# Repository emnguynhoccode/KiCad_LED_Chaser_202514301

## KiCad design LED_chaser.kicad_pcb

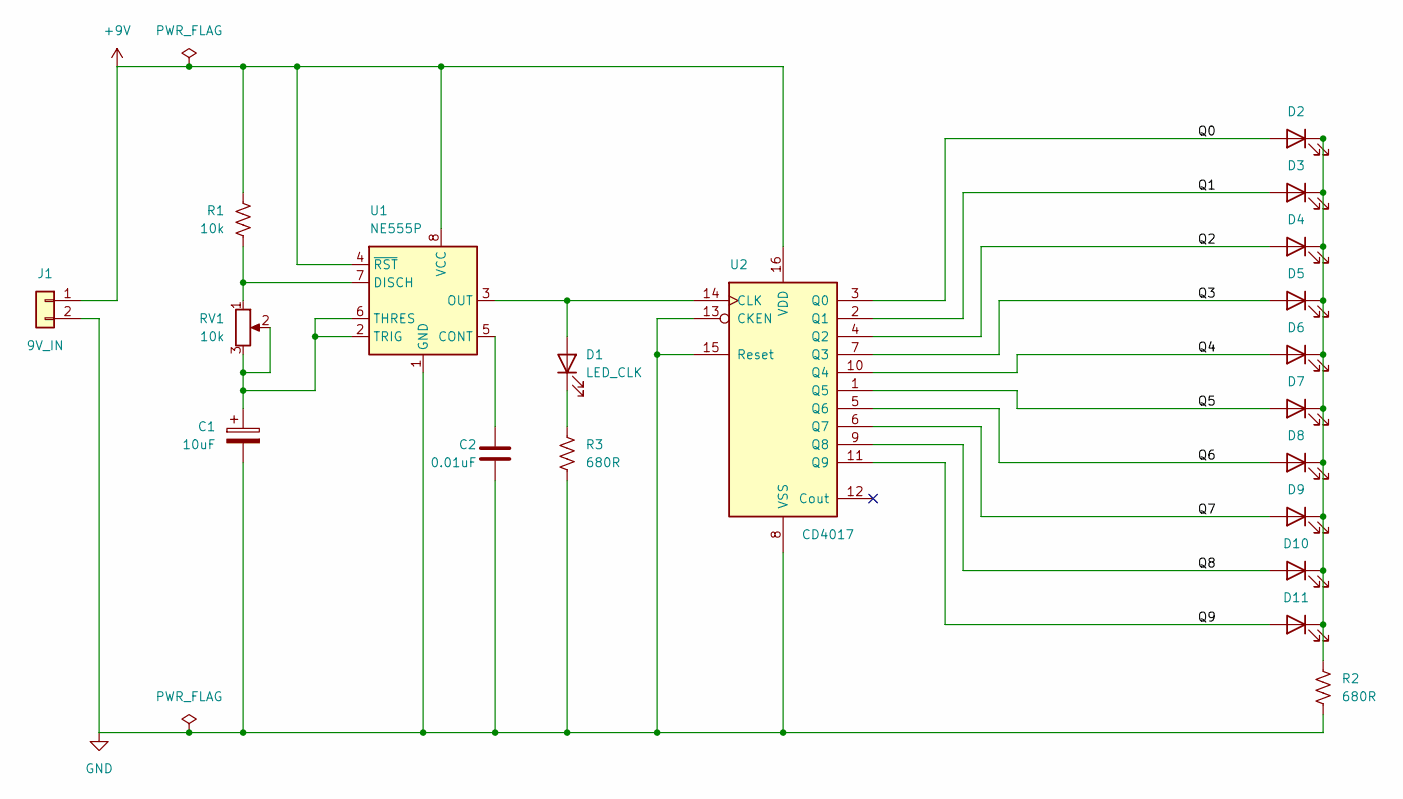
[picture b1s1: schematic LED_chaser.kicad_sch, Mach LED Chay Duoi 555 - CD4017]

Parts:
C1: 10uF; CP_Radial_D5.0mm_P2.50mm
C2: 0.01uF; C_Disc_D5.0mm_W2.5mm_P2.50mm
D1: LED_CLK; LED_D5.0mm
D2, D3, D4, D5, D6, D7, D8, D9, D10, D11: LED; LED_D5.0mm
J1: 9V_IN; PinHeader_1x02_P2.54mm_Vertical
R1: 10k; R_Axial_DIN0207_L6.3mm_D2.5mm_P10.16mm_Horizontal
R2, R3: 680R; R_Axial_DIN0207_L6.3mm_D2.5mm_P10.16mm_Horizontal
RV1: 10k; Potentiometer_Bourns_3386P_Vertical
U1: NE555P; DIP-8_W7.62mm
U2: CD4017; DIP-16_W7.62mm

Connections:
+9V: J1.1, R1.1, U1.4 (~RST), U1.8 (VCC), U2.16 (VDD)
/Q0: D2.2 (A), U2.3 (Q0)
/Q1: D3.2 (A), U2.2 (Q1)
/Q2: D4.2 (A), U2.4 (Q2)
/Q3: D5.2 (A), U2.7 (Q3)
/Q4: D6.2 (A), U2.10 (Q4)
/Q5: D7.2 (A), U2.1 (Q5)
/Q6: D8.2 (A), U2.5 (Q6)
/Q7: D9.2 (A), U2.6 (Q7)
/Q8: D10.2 (A), U2.9 (Q8)
/Q9: D11.2 (A), U2.11 (Q9)
GND: C1.2, C2.2, J1.2, R2.2, R3.2, U1.1 (GND), U2.8 (VSS), U2.13 (CKEN), U2.15 (Reset)
unnamed: D1.2 (A), U1.3 (OUT), U2.14 (CLK)
unnamed: D1.1 (K), R3.1
unnamed: D2.1 (K), D3.1 (K), D4.1 (K), D5.1 (K), D6.1 (K), D7.1 (K), D8.1 (K), D9.1 (K), D10.1 (K), D11.1 (K), R2.1
unnamed: C2.1, U1.5 (CONT)
unnamed: R1.2, RV1.1, U1.7 (DISCH)
unnamed: C1.1, RV1.2, RV1.3, U1.2 (TRIG), U1.6 (THRES)

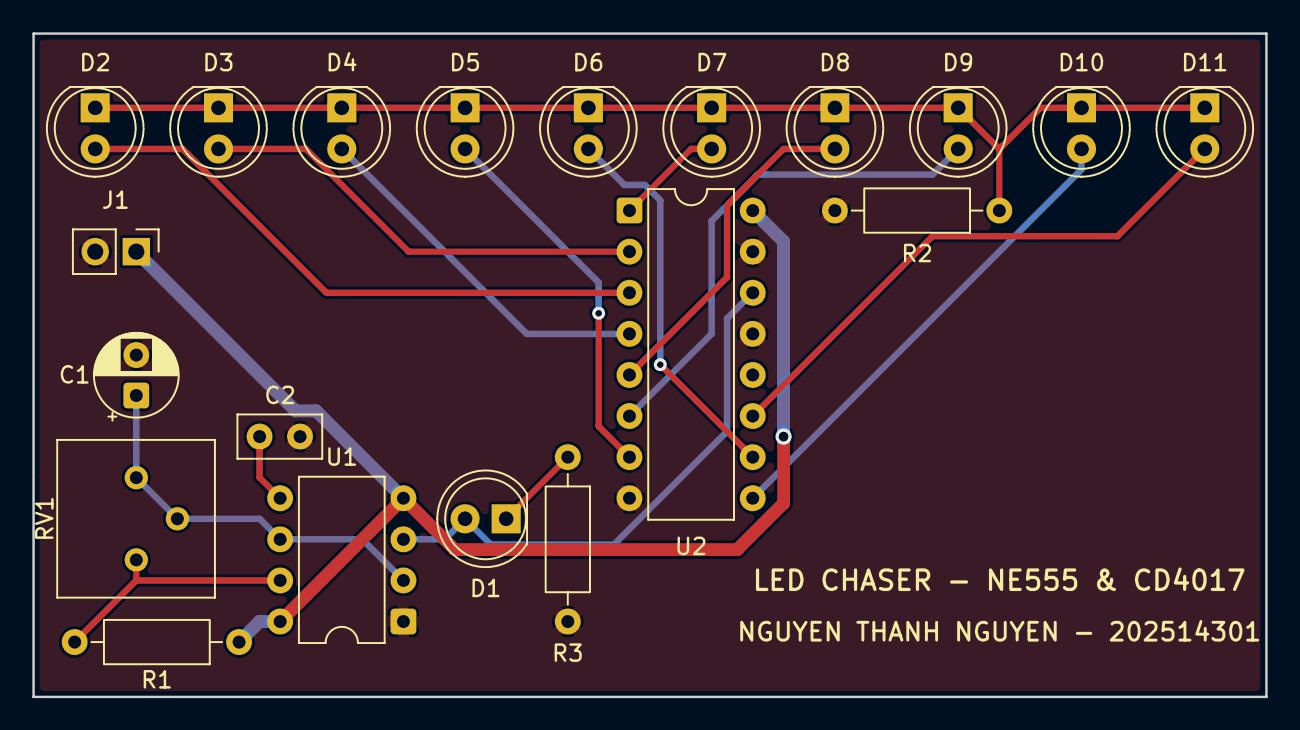
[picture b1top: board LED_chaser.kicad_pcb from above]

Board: 2 copper layers, 76.2 x 41.0 mm, 20 parts (0 on the bottom side), 18 nets.

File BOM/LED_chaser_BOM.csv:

"Reference","Value","Footprint","Quantity","Datasheet"
"C1","10uF","LED_Chaser_Fp:CP_Radial_D5.0mm_P2.50mm","1",""
"C2","0.01uF","LED_Chaser_Fp:C_Disc_D5.0mm_W2.5mm_P2.50mm","1",""
"D1","LED_CLK","LED_Chaser_Fp:LED_D5.0mm","1",""
"D2-D11","LED","LED_Chaser_Fp:LED_D5.0mm","10",""
"J1","9V_IN","LED_Chaser_Fp:PinHeader_1x02_P2.54mm_Vertical","1",""
"R1","10k","LED_Chaser_Fp:R_Axial_DIN0207_L6.3mm_D2.5mm_P10.16mm_Horizontal","1",""
"R2,R3","680R","LED_Chaser_Fp:R_Axial_DIN0207_L6.3mm_D2.5mm_P10.16mm_Horizontal","2",""
"RV1","10k","LED_Chaser_Fp:Potentiometer_Bourns_3386P_Vertical","1",""
"U1","NE555P","LED_Chaser_Fp:DIP-8_W7.62mm","1",""
"U2","CD4017","LED_Chaser_Fp:DIP-16_W7.62mm","1",""
